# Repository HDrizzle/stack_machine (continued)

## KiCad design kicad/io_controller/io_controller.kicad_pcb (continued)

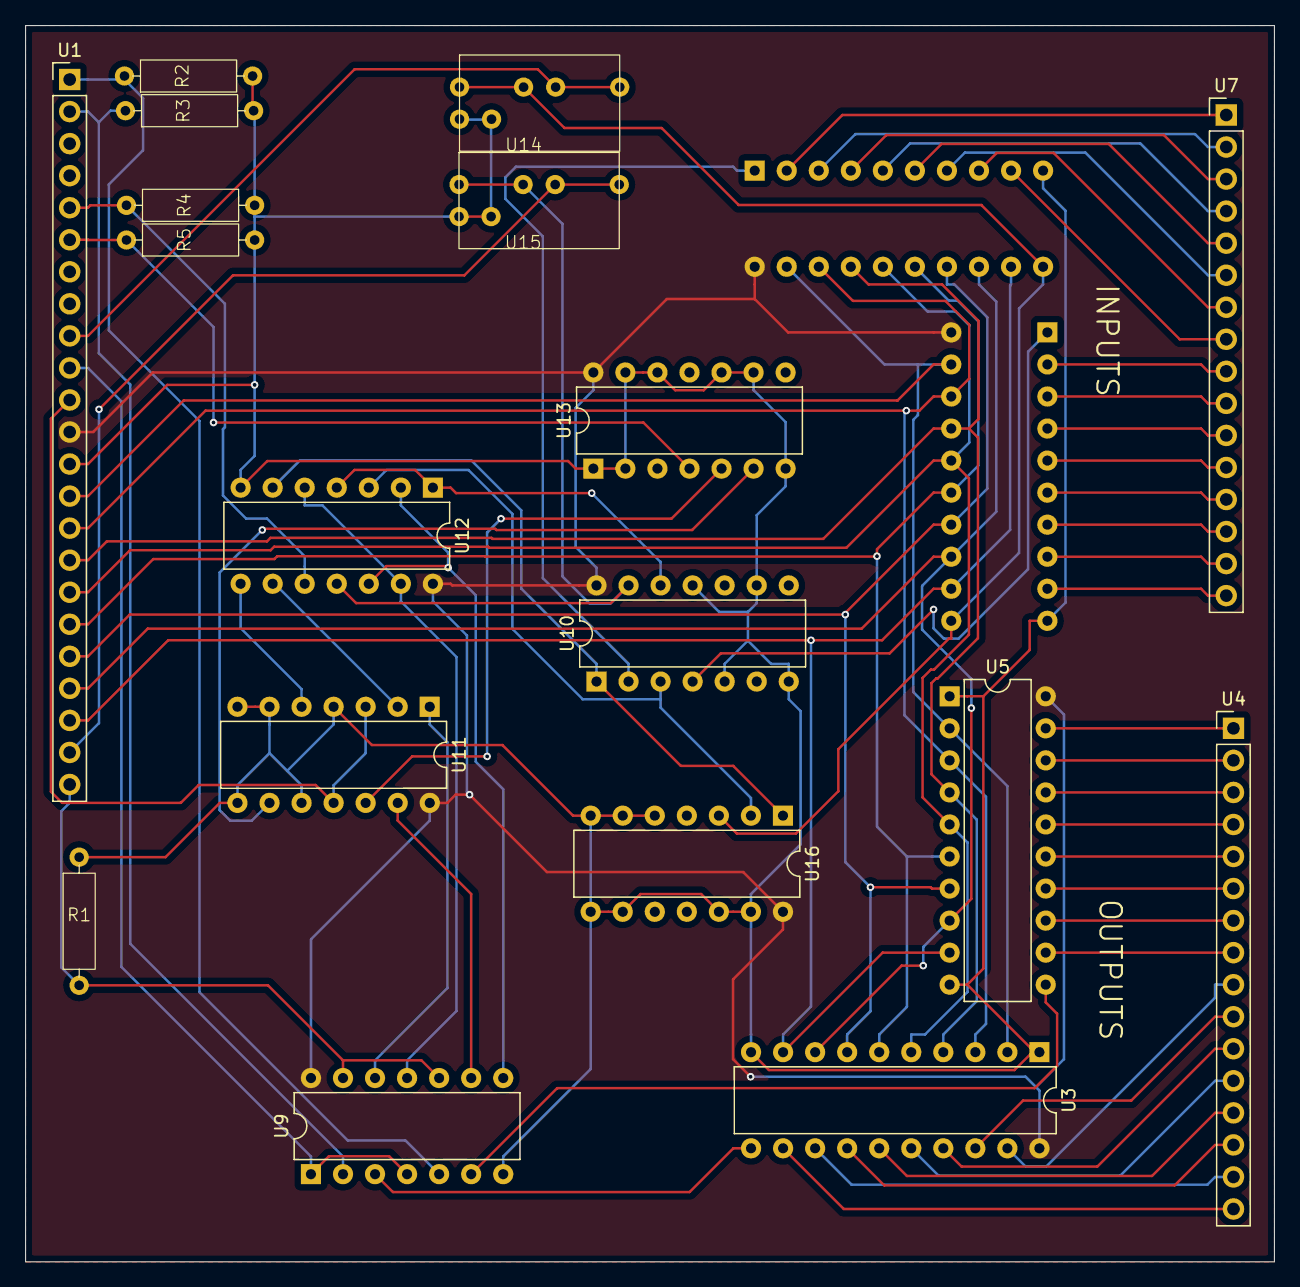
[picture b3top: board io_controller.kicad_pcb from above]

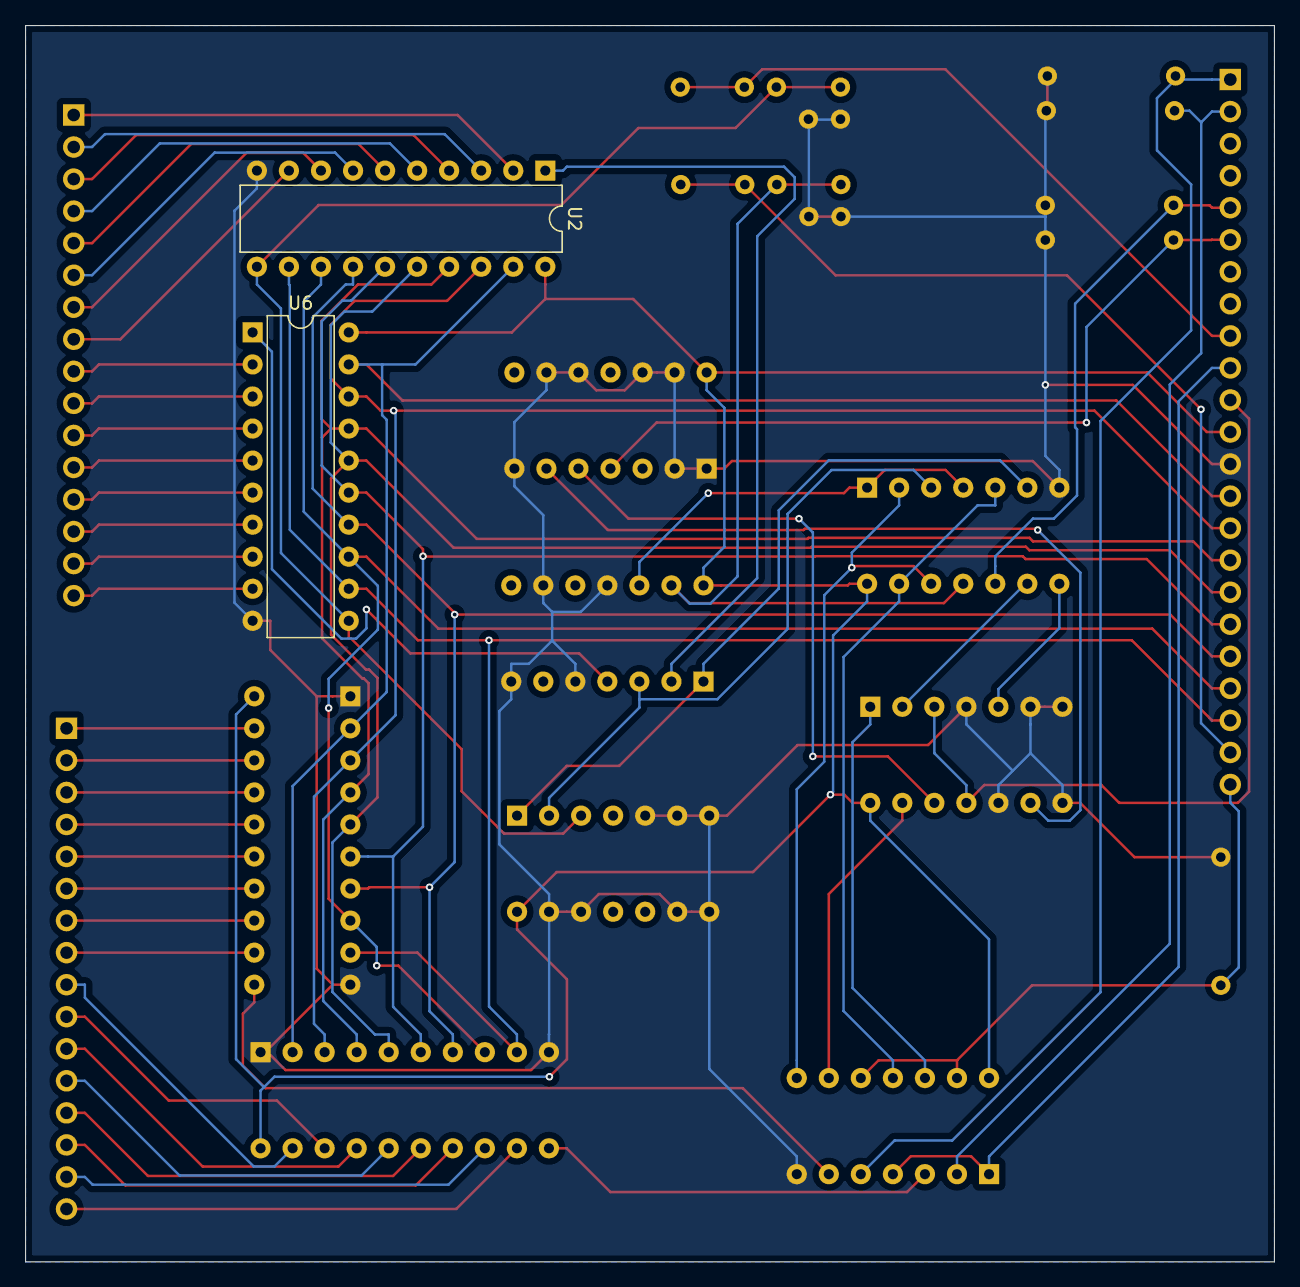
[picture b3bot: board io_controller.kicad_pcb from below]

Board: 2 copper layers, 99.0 x 98.0 mm, 20 parts (2 on the bottom side), 68 nets.

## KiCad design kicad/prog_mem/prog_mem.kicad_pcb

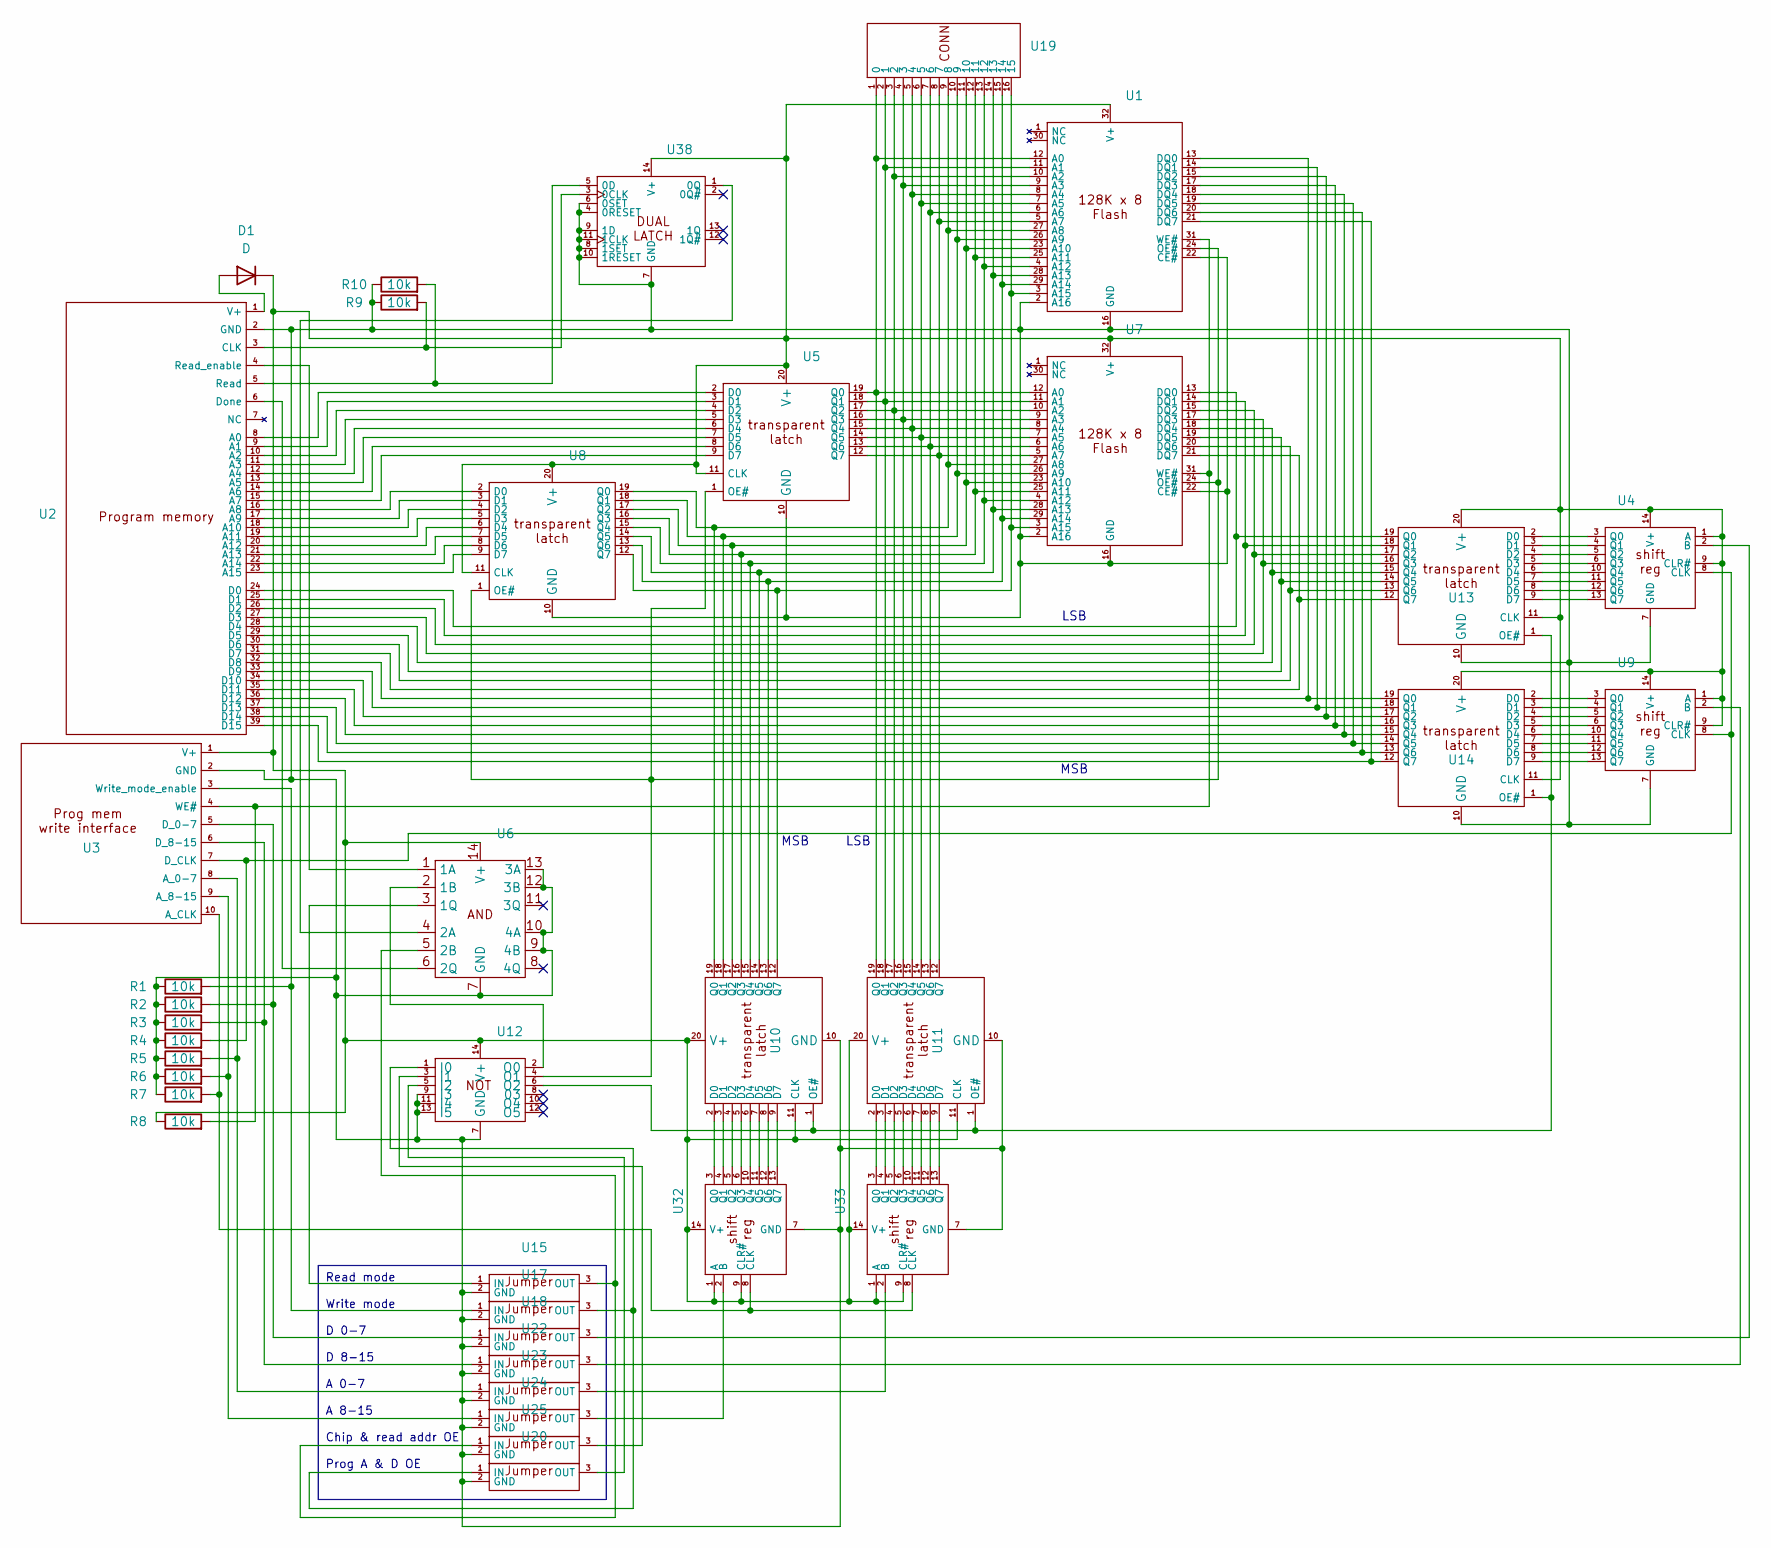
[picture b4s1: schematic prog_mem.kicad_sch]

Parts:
D1: D; D_A-405_P7.62mm_Horizontal
R1, R2, R3, R4, R5, R6, R7, R8, R9, R10: 10k; 0.4_pitch_resistor
U1, U7: DIP-32_W15.24mm
U2: PinHeader_1x39_P2.54mm_Vertical
U3: PinHeader_1x10_P2.54mm_Horizontal
U4, U6, U9, U12, U32, U33, U38: DIP-14_W7.62mm
U5, U8, U10, U11, U13, U14: DIP-20_W7.62mm
U15, U17, U18, U20, U22, U23, U24, U25: jumper
U19: PinHeader_1x16_P2.54mm_Vertical

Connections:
unnamed: D1.2 (A), U2.1 (V+)
unnamed: D1.1 (K), R8.1, U1.32 (V+), U3.1 (V+), U4.1 (A), U4.9 (CLR#), U4.14 (V+), U5.11 (CLK), U5.20 (V+), U6.14 (V+), U7.32 (V+), U8.11 (CLK), U8.20 (V+), U9.1 (A), U9.9 (CLR#), U9.14 (V+), U10.11 (CLK), U10.20 (V+), U11.11 (CLK), U11.20 (V+), U12.14 (V+), U13.11 (CLK), U13.20 (V+), U14.11 (CLK), U14.20 (V+), U32.1 (A), U32.9 (CLR#), U32.14 (V+), U33.1 (A), U33.9 (CLR#), U33.14 (V+), U38.14 (V+)
unnamed: U1.12 (A0), U5.19 (Q0), U7.12 (A0), U11.19 (Q0), U19.1 (0)
unnamed: U1.11 (A1), U5.18 (Q1), U7.11 (A1), U11.18 (Q1), U19.2 (1)
unnamed: U1.10 (A2), U5.17 (Q2), U7.10 (A2), U11.17 (Q2), U19.3 (2)
unnamed: U1.9 (A3), U5.16 (Q3), U7.9 (A3), U11.16 (Q3), U19.4 (3)
unnamed: U1.8 (A4), U5.15 (Q4), U7.8 (A4), U11.15 (Q4), U19.5 (4)
unnamed: U1.7 (A5), U5.14 (Q5), U7.7 (A5), U11.14 (Q5), U19.6 (5)
unnamed: U1.6 (A6), U5.13 (Q6), U7.6 (A6), U11.13 (Q6), U19.7 (6)
unnamed: U1.5 (A7), U5.12 (Q7), U7.5 (A7), U11.12 (Q7), U19.8 (7)
unnamed: U1.27 (A8), U7.27 (A8), U8.19 (Q0), U10.19 (Q0), U19.9 (8)
unnamed: U1.26 (A9), U7.26 (A9), U8.18 (Q1), U10.18 (Q1), U19.10 (9)
unnamed: U1.23 (A10), U7.23 (A10), U8.17 (Q2), U10.17 (Q2), U19.11 (10)
unnamed: U1.25 (A11), U7.25 (A11), U8.16 (Q3), U10.16 (Q3), U19.12 (11)
unnamed: U1.4 (A12), U7.4 (A12), U8.15 (Q4), U10.15 (Q4), U19.13 (12)
unnamed: U1.28 (A13), U7.28 (A13), U8.14 (Q5), U10.14 (Q5), U19.14 (13)
unnamed: U1.29 (A14), U7.29 (A14), U8.13 (Q6), U10.13 (Q6), U19.15 (14)
unnamed: U1.3 (A15), U7.3 (A15), U8.12 (Q7), U10.12 (Q7), U19.16 (15)
unnamed: R1.1, R2.1, R3.1, R4.1, R5.1, R6.1, R7.1, R9.1, R10.1, U1.2 (A16), U1.16 (GND), U1.22 (CE#), U2.2 (GND), U3.2 (GND), U4.7 (GND), U5.10 (GND), U6.7 (GND), U6.9 (4B), U6.10 (4A), U6.12 (3B), U6.13 (3A), U7.2 (A16), U7.16 (GND), U7.22 (CE#), U8.10 (GND), U9.7 (GND), U10.10 (GND), U11.10 (GND), U12.7 (GND), U12.9 (I3), U12.11 (I4), U12.13 (I5), U13.10 (GND), U14.10 (GND), U15.2 (GND), U17.2 (GND), U18.2 (GND), U20.2 (GND), U22.2 (GND), U23.2 (GND), U24.2 (GND), U25.2 (GND), U32.7 (GND), U33.7 (GND), U38.4 (0RESET), U38.6 (0SET), U38.7 (GND), U38.8 (1SET), U38.9 (1D), U38.10 (1RESET), U38.11 (1CLK)
unnamed: U1.13 (DQ0), U2.32 (D8), U14.19 (Q0)
unnamed: U1.14 (DQ1), U2.33 (D9), U14.18 (Q1)
unnamed: U1.15 (DQ2), U2.34 (D10), U14.17 (Q2)
unnamed: U1.17 (DQ3), U2.35 (D11), U14.16 (Q3)
unnamed: U1.18 (DQ4), U2.36 (D12), U14.15 (Q4)
unnamed: U1.19 (DQ5), U2.37 (D13), U14.14 (Q5)
unnamed: U1.20 (DQ6), U2.38 (D14), U14.13 (Q6)
unnamed: U1.21 (DQ7), U2.39 (D15), U14.12 (Q7)
unnamed: U1.24 (OE#), U5.1 (OE#), U7.24 (OE#), U8.1 (OE#), U12.4 (O1)
unnamed: R8.2, U1.31 (WE#), U3.4 (WE#), U7.31 (WE#)
unnamed: U2.8 (A0), U5.2 (D0)
unnamed: U2.9 (A1), U5.3 (D1)
unnamed: U2.10 (A2), U5.4 (D2)
unnamed: U2.11 (A3), U5.5 (D3)
unnamed: U2.12 (A4), U5.6 (D4)
unnamed: U2.13 (A5), U5.7 (D5)
unnamed: U2.14 (A6), U5.8 (D6)
unnamed: U2.15 (A7), U5.9 (D7)
unnamed: U2.16 (A8), U8.2 (D0)
unnamed: U2.17 (A9), U8.3 (D1)
unnamed: U2.18 (A10), U8.4 (D2)
unnamed: U2.19 (A11), U8.5 (D3)
unnamed: U2.20 (A12), U8.6 (D4)
unnamed: U2.21 (A13), U8.7 (D5)
unnamed: U2.22 (A14), U8.8 (D6)
unnamed: U2.23 (A15), U8.9 (D7)
unnamed: R9.2, U2.3 (CLK), U38.3 (0CLK)
unnamed: U2.6 (Done), U6.6 (2Q)
unnamed: R10.2, U2.5 (Read), U38.5 (0D)
unnamed: U2.4 (Read_enable), U6.1 (1A)
unnamed: R7.2, U3.10 (A_CLK), U32.8 (CLK), U33.8 (CLK)
unnamed: R4.2, U3.7 (D_CLK), U4.8 (CLK), U9.8 (CLK)
unnamed: U10.2 (D0), U32.3 (Q0)
unnamed: U10.3 (D1), U32.4 (Q1)
unnamed: U10.4 (D2), U32.5 (Q2)
unnamed: U10.5 (D3), U32.6 (Q3)
unnamed: U10.6 (D4), U32.10 (Q4)
unnamed: U10.7 (D5), U32.11 (Q5)
unnamed: U10.8 (D6), U32.12 (Q6)
unnamed: U10.9 (D7), U32.13 (Q7)
unnamed: U10.1 (OE#), U11.1 (OE#), U12.6 (O2), U13.1 (OE#), U14.1 (OE#)
unnamed: U11.2 (D0), U33.3 (Q0)
unnamed: U11.3 (D1), U33.4 (Q1)
unnamed: U11.4 (D2), U33.5 (Q2)
unnamed: U11.5 (D3), U33.6 (Q3)
unnamed: U11.6 (D4), U33.10 (Q4)
unnamed: U11.7 (D5), U33.11 (Q5)
unnamed: U11.8 (D6), U33.12 (Q6)
unnamed: U11.9 (D7), U33.13 (Q7)
unnamed: U12.1 (I0), U17.3 (OUT), U20.1 (IN)
unnamed: U12.3 (I1), U25.3 (OUT)
unnamed: U12.5 (I2), U20.3 (OUT)
unnamed: U6.2 (1B), U12.2 (O0)
unnamed: U4.3 (Q0), U13.2 (D0)
unnamed: U4.4 (Q1), U13.3 (D1)
unnamed: U4.5 (Q2), U13.4 (D2)
unnamed: U4.6 (Q3), U13.5 (D3)
unnamed: U4.10 (Q4), U13.6 (D4)
unnamed: U4.11 (Q5), U13.7 (D5)
unnamed: U4.12 (Q6), U13.8 (D6)
unnamed: U4.13 (Q7), U13.9 (D7)
unnamed: U2.24 (D0), U7.13 (DQ0), U13.19 (Q0)
unnamed: U2.25 (D1), U7.14 (DQ1), U13.18 (Q1)
unnamed: U2.26 (D2), U7.15 (DQ2), U13.17 (Q2)
unnamed: U2.27 (D3), U7.17 (DQ3), U13.16 (Q3)
unnamed: U2.28 (D4), U7.18 (DQ4), U13.15 (Q4)
unnamed: U2.29 (D5), U7.19 (DQ5), U13.14 (Q5)
unnamed: U2.30 (D6), U7.20 (DQ6), U13.13 (Q6)
unnamed: U2.31 (D7), U7.21 (DQ7), U13.12 (Q7)
unnamed: U9.3 (Q0), U14.2 (D0)
unnamed: U9.4 (Q1), U14.3 (D1)
unnamed: U9.5 (Q2), U14.4 (D2)
unnamed: U9.6 (Q3), U14.5 (D3)
unnamed: U9.10 (Q4), U14.6 (D4)
unnamed: U9.11 (Q5), U14.7 (D5)
unnamed: U9.12 (Q6), U14.8 (D6)
unnamed: U9.13 (Q7), U14.9 (D7)
unnamed: U6.3 (1Q), U15.1 (IN)
unnamed: U6.5 (2B), U15.3 (OUT), U25.1 (IN)
unnamed: R1.2, U3.3 (Write_mode_enable), U17.1 (IN)
unnamed: R2.2, U3.5 (D_0-7), U18.1 (IN)
unnamed: U4.2 (B), U18.3 (OUT)
unnamed: R3.2, U3.6 (D_8-15), U22.1 (IN)
unnamed: U9.2 (B), U22.3 (OUT)
unnamed: R5.2, U3.8 (A_0-7), U23.1 (IN)
unnamed: U23.3 (OUT), U33.2 (B)
unnamed: R6.2, U3.9 (A_8-15), U24.1 (IN)
unnamed: U24.3 (OUT), U32.2 (B)
unnamed: U6.4 (2A), U38.1 (0Q)

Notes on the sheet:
Read mode Write mode D 0-7 D 8-15 A 0-7 A 8-15 Chip & read addr OE Prog A & D OE
LSB
MSB

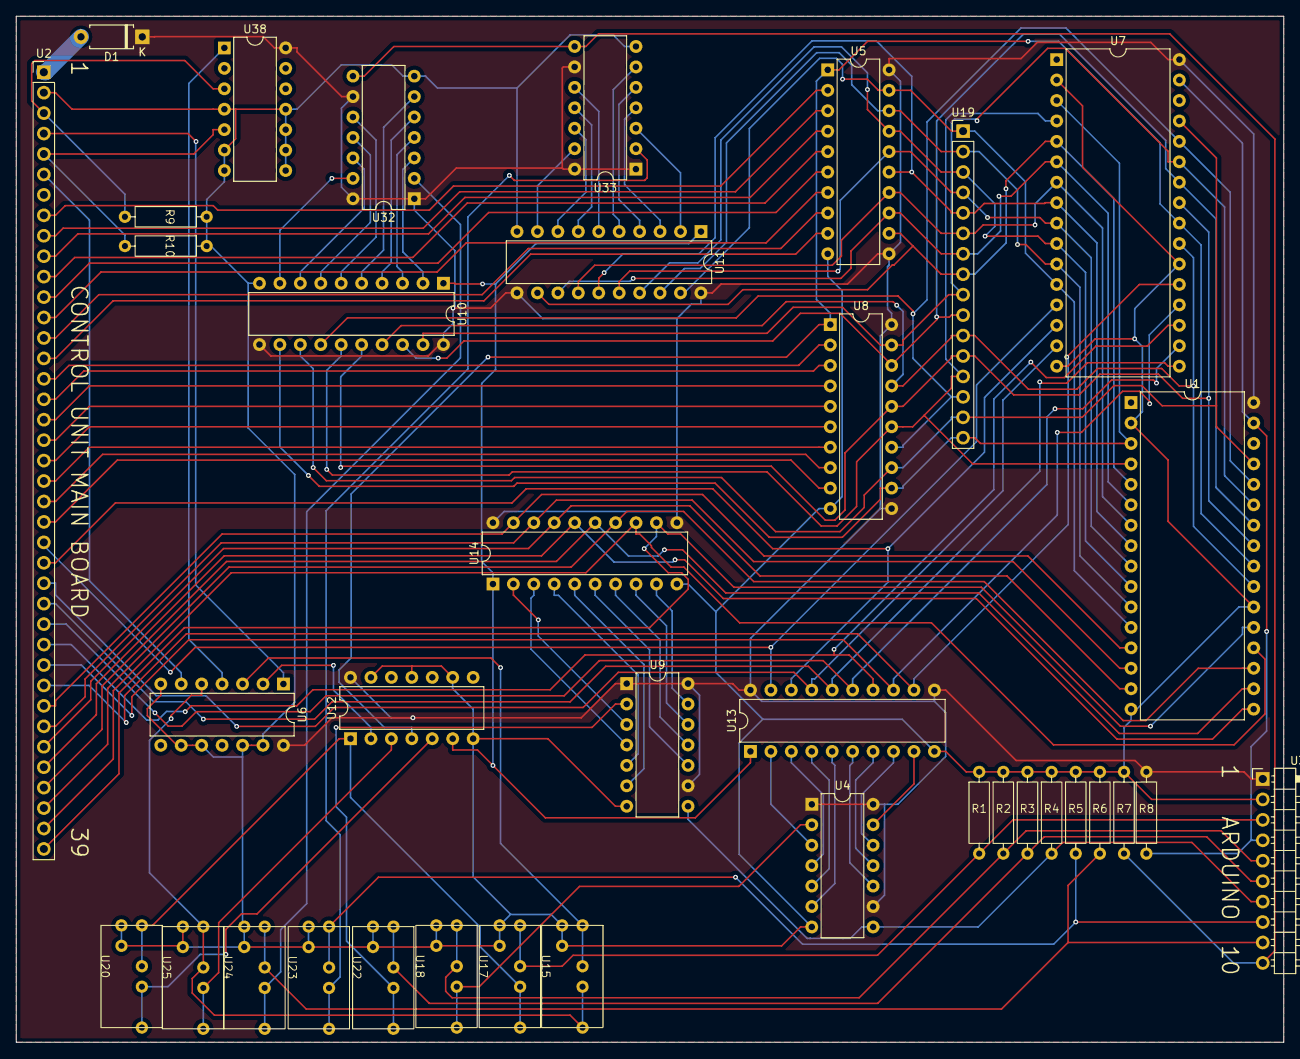
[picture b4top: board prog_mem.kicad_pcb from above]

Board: 2 copper layers, 157.5 x 127.5 mm, 37 parts (0 on the bottom side), 108 nets.

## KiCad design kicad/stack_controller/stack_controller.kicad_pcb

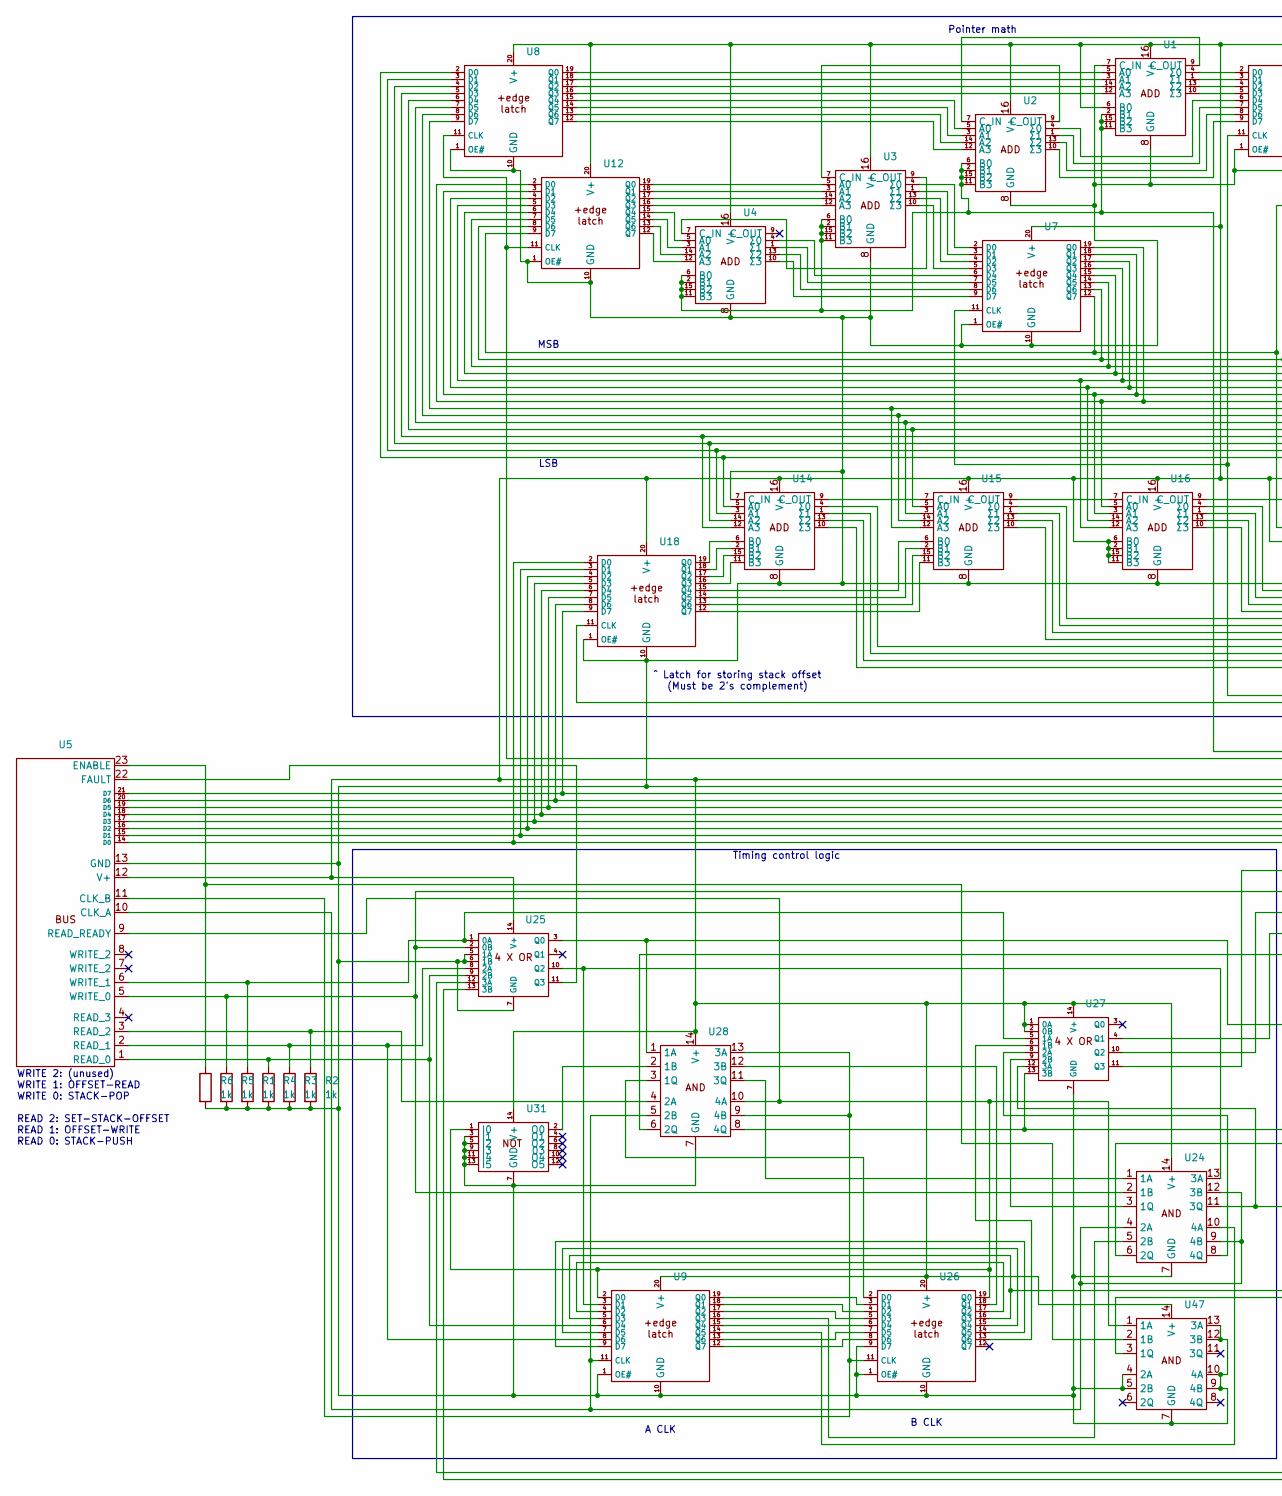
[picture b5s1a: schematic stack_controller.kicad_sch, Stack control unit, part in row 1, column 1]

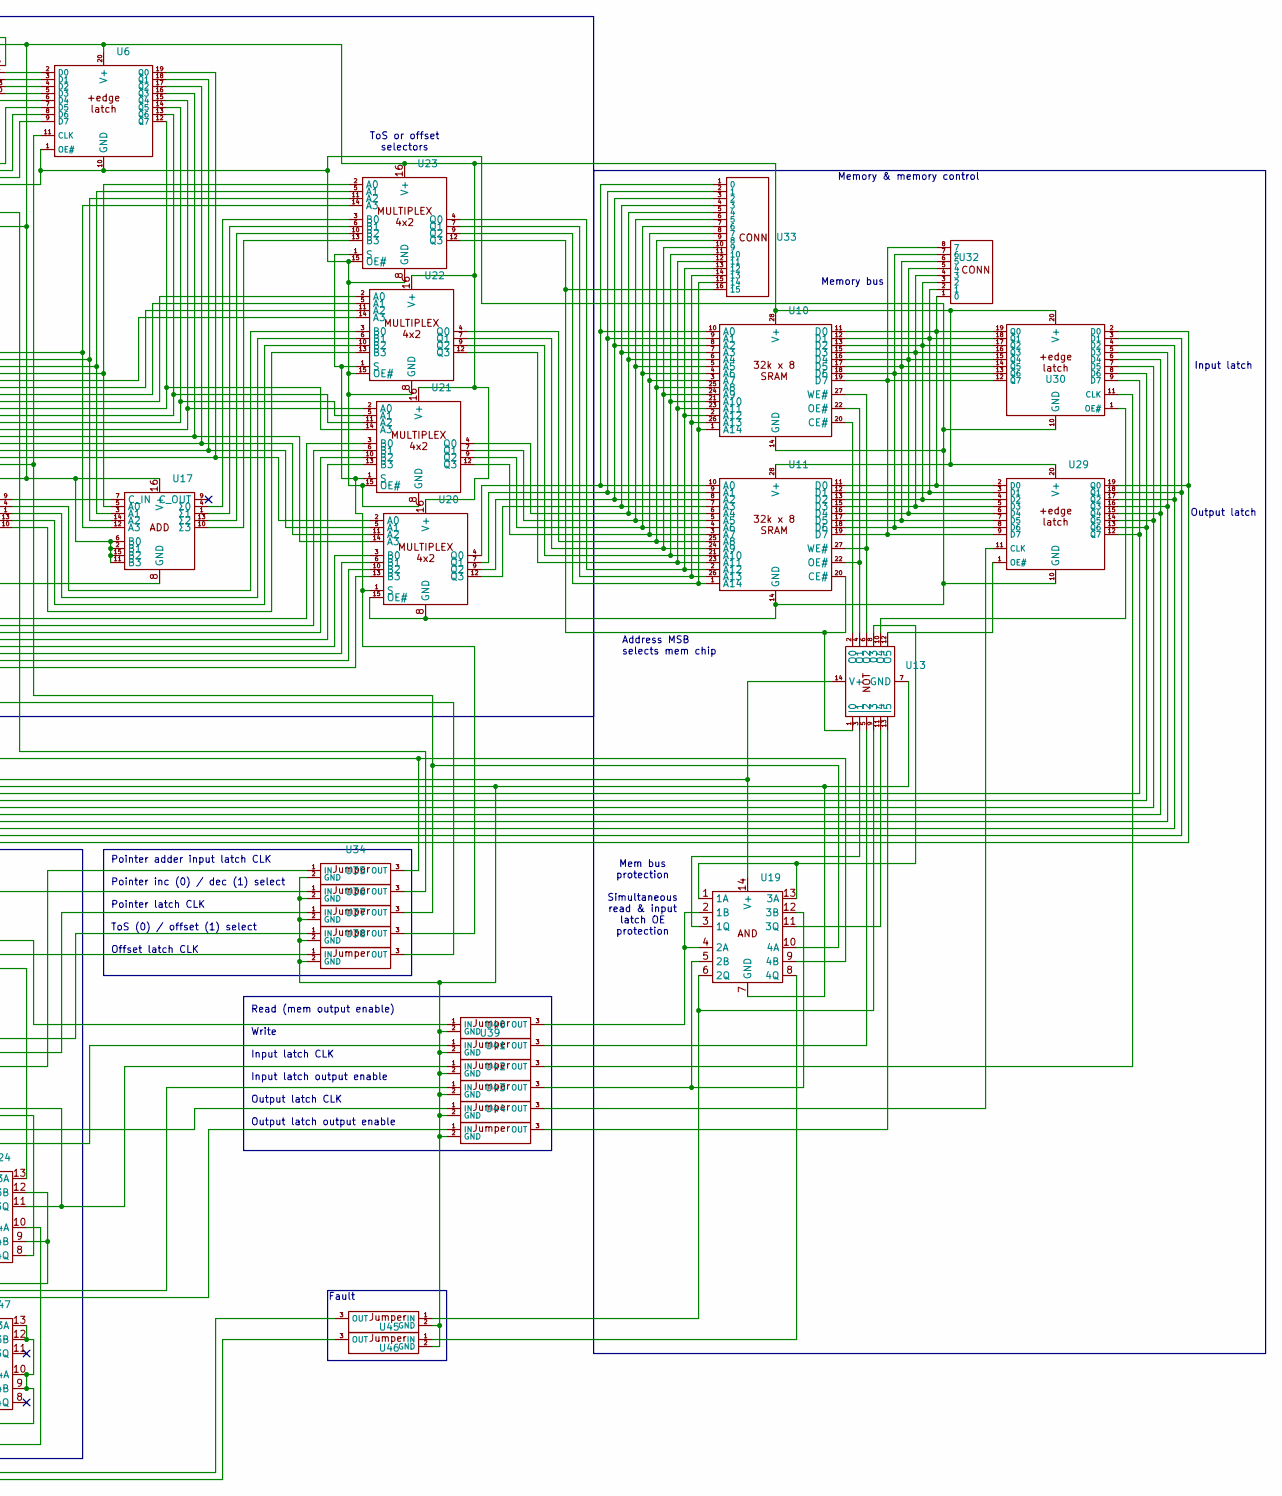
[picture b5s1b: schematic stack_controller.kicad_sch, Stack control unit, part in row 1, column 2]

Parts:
R1, R2, R3, R4, R5, R6: 1k; 0.4_pitch_resistor
U1, U2, U3, U4, U14, U15, U16, U17, U20, U21, U22, U23: DIP-16_W7.62mm
U5: PinHeader_1x23_P2.54mm_Vertical
U6, U7, U8, U9, U12, U18, U26, U29, U30: DIP-20_W7.62mm
U10, U11: DIP-28_W15.24mm
U13, U19, U24, U25, U27, U28, U31, U47: DIP-14_W7.62mm
U32: PinHeader_1x08_P2.54mm_Vertical
U33: PinHeader_1x16_P2.54mm_Vertical
U34, U35, U36, U37, U38, U39, U40, U41, U42, U43, U44, U45, U46: jumper

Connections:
unnamed: U1.5 (A0), U8.19 (Q0)
unnamed: U1.3 (A1), U8.18 (Q1)
unnamed: U1.14 (A2), U8.17 (Q2)
unnamed: U1.12 (A3), U8.16 (Q3)
unnamed: U1.2 (B1), U1.11 (B3), U1.15 (B2), U2.2 (B1), U2.6 (B0), U2.11 (B3), U2.15 (B2), U3.2 (B1), U3.6 (B0), U3.11 (B3), U3.15 (B2), U4.2 (B1), U4.6 (B0), U4.11 (B3), U4.15 (B2), U35.3 (OUT)
unnamed: U1.9 (C_OUT), U2.7 (C_IN)
unnamed: U1.4 (Σ0), U6.2 (D0)
unnamed: U1.1 (Σ1), U6.3 (D1)
unnamed: U1.13 (Σ2), U6.4 (D2)
unnamed: U1.10 (Σ3), U6.5 (D3)
unnamed: U2.5 (A0), U8.15 (Q4)
unnamed: U2.3 (A1), U8.14 (Q5)
unnamed: U2.14 (A2), U8.13 (Q6)
unnamed: U2.12 (A3), U8.12 (Q7)
unnamed: U2.9 (C_OUT), U3.7 (C_IN)
unnamed: U2.4 (Σ0), U6.6 (D4)
unnamed: U2.1 (Σ1), U6.7 (D5)
unnamed: U2.13 (Σ2), U6.8 (D6)
unnamed: U2.10 (Σ3), U6.9 (D7)
unnamed: U3.9 (C_OUT), U4.7 (C_IN)
unnamed: U3.4 (Σ0), U7.2 (D0)
unnamed: U3.1 (Σ1), U7.3 (D1)
unnamed: U3.13 (Σ2), U7.4 (D2)
unnamed: U3.10 (Σ3), U7.5 (D3)
unnamed: U4.4 (Σ0), U7.6 (D4)
unnamed: U4.1 (Σ1), U7.7 (D5)
unnamed: U4.13 (Σ2), U7.8 (D6)
unnamed: U4.10 (Σ3), U7.9 (D7)
unnamed: U10.10 (A0), U11.10 (A0), U20.4 (Q0), U33.1 (0)
unnamed: U10.9 (A1), U11.9 (A1), U20.7 (Q1), U33.2 (1)
unnamed: U10.8 (A2), U11.8 (A2), U20.9 (Q2), U33.3 (2)
unnamed: U10.7 (A3), U11.7 (A3), U20.12 (Q3), U33.4 (3)
unnamed: U10.6 (A4), U11.6 (A4), U21.4 (Q0), U33.5 (4)
unnamed: U10.5 (A5), U11.5 (A5), U21.7 (Q1), U33.6 (5)
unnamed: U10.4 (A6), U11.4 (A6), U21.9 (Q2), U33.7 (6)
unnamed: U10.3 (A7), U11.3 (A7), U21.12 (Q3), U33.8 (7)
unnamed: U10.25 (A8), U11.25 (A8), U22.4 (Q0), U33.9 (8)
unnamed: U10.24 (A9), U11.24 (A9), U22.7 (Q1), U33.10 (9)
unnamed: U10.21 (A10), U11.21 (A10), U22.9 (Q2), U33.11 (10)
unnamed: U10.23 (A11), U11.23 (A11), U22.12 (Q3), U33.12 (11)
unnamed: U10.2 (A12), U11.2 (A12), U23.4 (Q0), U33.13 (12)
unnamed: U10.26 (A13), U11.26 (A13), U23.7 (Q1), U33.14 (13)
unnamed: U10.1 (A14), U11.1 (A14), U23.9 (Q2), U33.15 (14)
unnamed: U10.20 (CE#), U13.2 (O0)
unnamed: U10.11 (D0), U11.11 (D0), U29.2 (D0), U30.19 (Q0), U32.1 (0)
unnamed: U10.12 (D1), U11.12 (D1), U29.3 (D1), U30.18 (Q1), U32.2 (1)
unnamed: U10.13 (D2), U11.13 (D2), U29.4 (D2), U30.17 (Q2), U32.3 (2)
unnamed: U10.15 (D3), U11.15 (D3), U29.5 (D3), U30.16 (Q3), U32.4 (3)
unnamed: U10.16 (D4), U11.16 (D4), U29.6 (D4), U30.15 (Q4), U32.5 (4)
unnamed: U10.17 (D5), U11.17 (D5), U29.7 (D5), U30.14 (Q5), U32.6 (5)
unnamed: U10.18 (D6), U11.18 (D6), U29.8 (D6), U30.13 (Q6), U32.7 (6)
unnamed: U10.19 (D7), U11.19 (D7), U29.9 (D7), U30.12 (Q7), U32.8 (7)
unnamed: U10.22 (OE#), U11.22 (OE#), U13.4 (O1)
unnamed: U10.27 (WE#), U11.27 (WE#), U13.6 (O2)
unnamed: U11.20 (CE#), U13.1 (I0), U23.12 (Q3), U33.16 (15)
unnamed: U8.11 (CLK), U12.11 (CLK), U19.9 (4B), U34.3 (OUT)
unnamed: U7.19 (Q0), U12.2 (D0), U16.5 (A0), U22.2 (A0)
unnamed: U7.18 (Q1), U12.3 (D1), U16.3 (A1), U22.5 (A1)
unnamed: U7.17 (Q2), U12.4 (D2), U16.14 (A2), U22.11 (A2)
unnamed: U7.16 (Q3), U12.5 (D3), U16.12 (A3), U22.14 (A3)
unnamed: U7.15 (Q4), U12.6 (D4), U17.5 (A0), U23.2 (A0)
unnamed: U7.14 (Q5), U12.7 (D5), U17.3 (A1), U23.5 (A1)
unnamed: U7.13 (Q6), U12.8 (D6), U17.14 (A2), U23.11 (A2)
unnamed: U7.12 (Q7), U12.9 (D7), U17.12 (A3), U23.14 (A3)
unnamed: U3.5 (A0), U12.19 (Q0)
unnamed: U3.3 (A1), U12.18 (Q1)
unnamed: U3.14 (A2), U12.17 (Q2)
unnamed: U3.12 (A3), U12.16 (Q3)
unnamed: U4.5 (A0), U12.15 (Q4)
unnamed: U4.3 (A1), U12.14 (Q5)
unnamed: U4.14 (A2), U12.13 (Q6)
unnamed: U4.12 (A3), U12.12 (Q7)
unnamed: U13.8 (03), U19.1 (1A), U19.13 (3A)
unnamed: U13.3 (I1), U19.3 (1Q)
unnamed: U13.5 (I2), U40.3 (OUT)
unnamed: U13.9 (I3), U19.6 (2Q), U45.1 (IN)
unnamed: U13.11 (I4), U19.11 (3Q)
unnamed: U13.13 (I5), U44.3 (OUT)
unnamed: U13.10 (O4), U30.1 (OE#)
unnamed: U13.12 (O5), U29.1 (OE#)
unnamed: U6.19 (Q0), U8.2 (D0), U14.5 (A0), U20.2 (A0)
unnamed: U6.18 (Q1), U8.3 (D1), U14.3 (A1), U20.5 (A1)
unnamed: U6.17 (Q2), U8.4 (D2), U14.14 (A2), U20.11 (A2)
unnamed: U6.16 (Q3), U8.5 (D3), U14.12 (A3), U20.14 (A3)
unnamed: U14.6 (B0), U18.19 (Q0)
unnamed: U14.2 (B1), U18.18 (Q1)
unnamed: U14.15 (B2), U18.17 (Q2)
unnamed: U14.11 (B3), U18.16 (Q3)
unnamed: U14.9 (C_OUT), U15.7 (C_IN)
unnamed: U14.4 (Σ0), U20.3 (B0)
unnamed: U14.1 (Σ1), U20.6 (B1)
unnamed: U14.13 (Σ2), U20.10 (B2)
unnamed: U14.10 (Σ3), U20.13 (B3)
unnamed: U6.15 (Q4), U8.6 (D4), U15.5 (A0), U21.2 (A0)
unnamed: U6.14 (Q5), U8.7 (D5), U15.3 (A1), U21.5 (A1)
unnamed: U6.13 (Q6), U8.8 (D6), U15.14 (A2), U21.11 (A2)
unnamed: U6.12 (Q7), U8.9 (D7), U15.12 (A3), U21.14 (A3)
unnamed: U15.6 (B0), U18.15 (Q4)
unnamed: U15.2 (B1), U18.14 (Q5)
unnamed: U15.15 (B2), U18.13 (Q6)
unnamed: U15.11 (B3), U18.12 (Q7)
unnamed: U15.9 (C_OUT), U16.7 (C_IN)
unnamed: U15.4 (Σ0), U21.3 (B0)
unnamed: U15.1 (Σ1), U21.6 (B1)
unnamed: U15.13 (Σ2), U21.10 (B2)
unnamed: U15.10 (Σ3), U21.13 (B3)
unnamed: U16.9 (C_OUT), U17.7 (C_IN)
unnamed: U16.4 (Σ0), U22.3 (B0)
unnamed: U16.1 (Σ1), U22.6 (B1)
unnamed: U16.13 (Σ2), U22.10 (B2)
unnamed: U16.10 (Σ3), U22.13 (B3)
unnamed: U17.4 (Σ0), U23.3 (B0)
unnamed: U17.1 (Σ1), U23.6 (B1)
unnamed: U17.13 (Σ2), U23.10 (B2)
unnamed: U17.10 (Σ3), U23.13 (B3)
unnamed: U18.11 (CLK), U38.3 (OUT)
unnamed: U5.14 (D0), U18.2 (D0), U29.19 (Q0), U30.2 (D0)
unnamed: U5.15 (D1), U18.3 (D1), U29.18 (Q1), U30.3 (D1)
unnamed: U5.16 (D2), U18.4 (D2), U29.17 (Q2), U30.4 (D2)
unnamed: U5.17 (D3), U18.5 (D3), U29.16 (Q3), U30.5 (D3)
unnamed: U5.18 (D4), U18.6 (D4), U29.15 (Q4), U30.6 (D4)
unnamed: U5.19 (D5), U18.7 (D5), U29.14 (Q5), U30.7 (D5)
unnamed: U5.20 (D6), U18.8 (D6), U29.13 (Q6), U30.8 (D6)
unnamed: U5.21 (D7), U18.9 (D7), U29.12 (Q7), U30.9 (D7)
unnamed: U19.2 (1B), U19.4 (2A), U39.3 (OUT)
unnamed: U19.5 (2B), U19.12 (3B), U42.3 (OUT)
unnamed: U6.11 (CLK), U7.11 (CLK), U19.10 (4A), U36.3 (OUT)
unnamed: U19.8 (4Q), U46.1 (IN)
unnamed: U20.1 (S), U21.1 (S), U22.1 (S), U23.1 (S), U37.3 (OUT)
unnamed: U24.1 (1A), U28.11 (3Q)
unnamed: R5.1, U5.5 (WRITE_0), U24.2 (1B), U25.2 (0B), U35.1 (IN)
unnamed: U24.3 (1Q), U27.9 (2B)
unnamed: U5.10 (CLK_A), U9.11 (CLK), U24.4 (2A), U24.9 (4B), U24.12 (3B), U28.5 (2B)
unnamed: U9.16 (Q3), U24.5 (2B)
unnamed: U24.6 (2Q), U40.1 (IN)
unnamed: U9.3 (D1), U24.13 (3A), U25.10 (Q2)
unnamed: U24.11 (3Q), U27.12 (3A), U41.1 (IN)
unnamed: U9.14 (Q5), U24.10 (4A)
unnamed: U24.8 (4Q), U27.8 (2A)
unnamed: R1.1, U5.6 (WRITE_1), U25.1 (0A), U27.5 (1A)
unnamed: R3.1, U5.2 (READ_1), U9.8 (D6), U25.8 (2A)
unnamed: R4.1, U5.1 (READ_0), U9.6 (D4), U25.9 (2B)
unnamed: U25.12 (3A), U45.3 (OUT)
unnamed: U25.13 (3B), U46.3 (OUT)
unnamed: U25.3 (Q0), U28.1 (1A), U39.1 (IN)
unnamed: U5.22 (FAULT), U25.11 (Q3)
unnamed: U5.11 (CLK_B), U26.11 (CLK), U28.9 (4B), U28.13 (3A)
unnamed: U26.2 (D0), U28.3 (1Q)
unnamed: U9.19 (Q0), U26.3 (D1)
unnamed: U9.18 (Q1), U26.4 (D2)
unnamed: U9.17 (Q2), U26.5 (D3)
unnamed: U9.15 (Q4), U26.6 (D4)
unnamed: U9.13 (Q6), U26.7 (D5)
unnamed: U9.12 (Q7), U26.8 (D6)
unnamed: U5.9 (READ_READY), U9.2 (D0), U26.19 (Q0), U28.10 (4A), U31.1 (I0), U47.1 (1A)
unnamed: U26.18 (Q1), U28.12 (3B)
unnamed: U9.4 (D2), U26.17 (Q2)
unnamed: U9.5 (D3), U26.16 (Q3), U42.1 (IN)
unnamed: U9.7 (D5), U26.15 (Q4)
unnamed: U9.9 (D7), U26.14 (Q5)
unnamed: U26.13 (Q6), U27.6 (1B)
unnamed: U27.13 (3B), U28.8 (4Q), U43.1 (IN)
unnamed: U27.4 (Q1), U37.1 (IN)
unnamed: U27.10 (Q2), U36.1 (IN)
unnamed: U27.11 (Q3), U34.1 (IN)
unnamed: U28.2 (1B), U31.2 (O0)
unnamed: R2.1, U5.3 (READ_2), U28.4 (2A)
unnamed: U28.6 (2Q), U38.1 (IN)
unnamed: U29.11 (CLK), U43.3 (OUT)
unnamed: U30.11 (CLK), U41.3 (OUT)
unnamed: U44.1 (IN), U47.3 (1Q)
unnamed: R6.1, U5.23 (ENABLE), U47.2 (1B)

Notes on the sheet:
Mem bus protection Simultaneous read & input latch OE protection
MSB
Pointer math
ToS or offset selectors
Output latch
LSB
Fault
Pointer adder input latch CLK Pointer inc (0) / dec (1) select Pointer latch CLK ToS (0) / offset (1) select Offset latch CLK
B CLK
WRITE 2: (unused) WRITE 1: OFFSET-READ WRITE 0: STACK-POP READ 2: SET-STACK-OFFSET READ 1: OFFSET-WRITE READ 0: STACK-PUSH
Address MSB selects mem chip
A CLK
Read (mem output enable) Write Input latch CLK Input latch output enable Output latch CLK Output latch output enable
Input latch
Timing control logic
Memory & memory control
Memory bus
^ Latch for storing stack offset (Must be 2's complement)

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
